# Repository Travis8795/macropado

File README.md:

# macropado
Macropado is a **8 key** macropad with a **rotary encoder** and an **OLED** screan and 8 SK6812 MINI-E Leds for **RGB** lights, it runs on **KMK** with python.

Here is a [video](https://youtu.be/G09okHm-6bo?si=OeQklzNeX-y66rIM) of it working

## CAD
Designed using **Fusion 360**.

The macropad is assembled by pressing heat-set inserts into the back of the top plate. Then, 16mm screws are inserted through the bottom of the base and the PCB, threading directly into the inserts to hold everything together.

| front | back |
| :---: | :---: |
|  |  |
|  |  |

## PCB
Designed using **KiCad**.

| Schematic | PCB |
| :---: | :---: |
|  |  |

## Firmware overview
Macropado runs on **KMK firmware** using CircuitPython for easy, "on-the-fly" customization.

* **Rotary Encoder:** Adjusts system volume with a press-to-mute function.
* **8 Programmable Keys:** Currently configured as custom macros for productivity.
* **OLED Screen:** Features a custom **Bongocat** animation! :3
* **RGB Lighting:** 8 addressable SK6812 MINI-E LEDs for dynamic status effects.

All logic is written in Python using KMK modules and extensions.

## BOM:
Here is **everything** you need to make this macropad

- 1x XIAO RP2040
- 8x Cherry MX Switches
- 8x DSA Keycaps
- 4x M3x5x4 Heatset inserts
- 4x M3x16mm screws
- 9x 1N4148 DO-35 Diodes.
- 8x SK6812 MINI-E LEDs
- 1x 0.91" 128x32 OLED Display
- 1x EC11 Rotary Encoder
- 1x Case (3 printed parts)

---
A huge shout-out to Hack Club and the Blueprint team!

I’ve dreamed of making this macropad for a long time, but I failed my previous attempts. Blueprint was the awesome opportunity I needed. The community support was amazing and helped me through the tough parts!

This was my first time ever using Fusion 360 for CAD, KiCad for PCB design, and my first time 'shipping' a complete GitHub repo. I learned so much during this YSWS journey. Thank you for everything—I owe you guys a lot! I'm so proud of my Macropado. <3

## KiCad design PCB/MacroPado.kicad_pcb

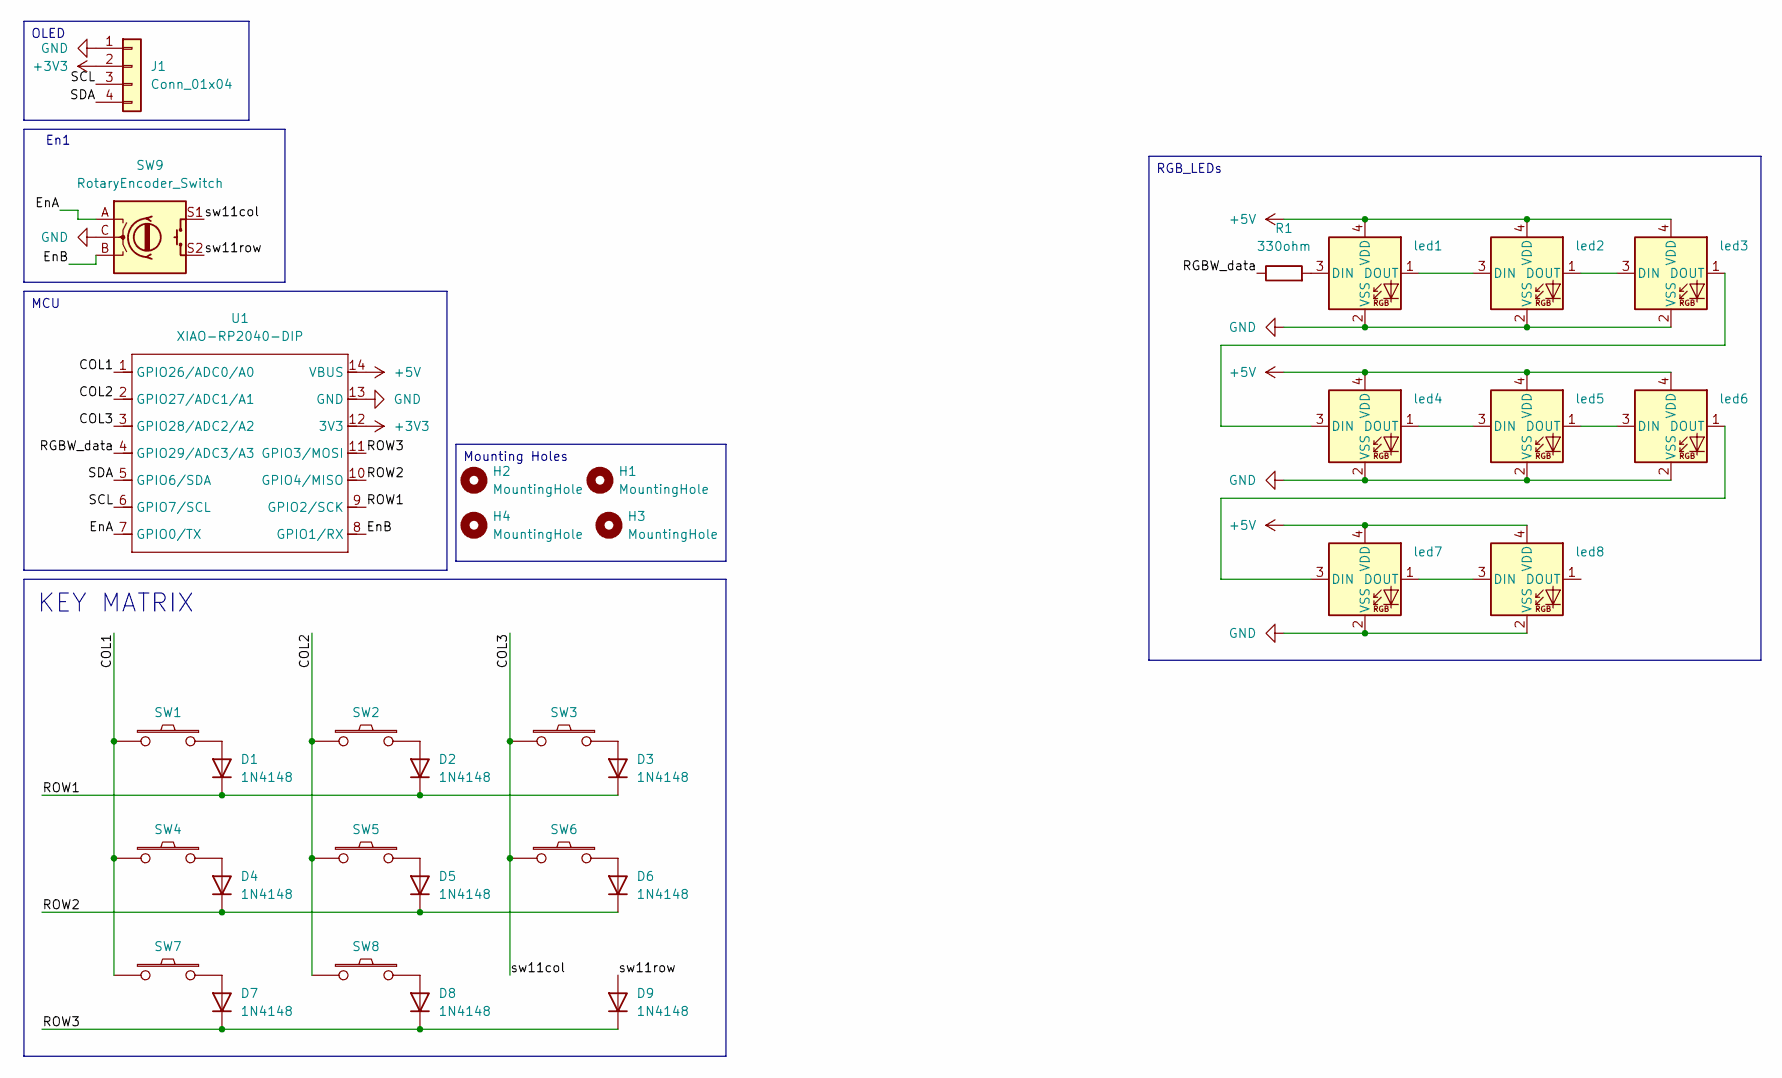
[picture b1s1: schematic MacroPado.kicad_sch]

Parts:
D1, D2, D3, D4, D5, D6, D7, D8, D9: 1N4148; D_DO-35_SOD27_P7.62mm_Horizontal
H1, H2, H3, H4: MountingHole; MountingHole_3.2mm_M3
J1: Conn_01x04; SSD1306-0.91-OLED-4pin-128x32
R1: 330ohm; R_Axial_DIN0204_L3.6mm_D1.6mm_P5.08mm_Horizontal
SW1, SW2, SW3, SW4, SW5, SW6, SW7, SW8: keyswitch; SW_Cherry_MX_1.00u_PCB; DigiKey Part Number MX2A-11NA
SW9: RotaryEncoder_Switch; RotaryEncoder_Alps_EC11E-Switch_Vertical_H20mm
U1: XIAO-RP2040-DIP
led1, led2, led3, led4, led5, led6, led7, led8: SK6812MINI; MX_SK6812MINI-E_REV

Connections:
+3V3: J1.2, U1.12 (3V3)
+5V: U1.14 (VBUS), led1.4 (VDD), led2.4 (VDD), led3.4 (VDD), led4.4 (VDD), led5.4 (VDD), led6.4 (VDD), led7.4 (VDD), led8.4 (VDD)
/COL1: SW1.2, SW4.2, SW7.2, U1.1 (GPIO26/ADC0/A0)
/COL2: SW2.2, SW5.2, SW8.2, U1.2 (GPIO27/ADC1/A1)
/COL3: SW3.2, SW6.2, SW9.S1, U1.3 (GPIO28/ADC2/A2)
/EnA: SW9.A, U1.7 (GPIO0/TX)
/EnB: SW9.B, U1.8 (GPIO1/RX)
/RGBW_data: R1.1, U1.4 (GPIO29/ADC3/A3)
/ROW1: D1.1 (K), D2.1 (K), D3.1 (K), U1.9 (GPIO2/SCK)
/ROW2: D4.1 (K), D5.1 (K), D6.1 (K), U1.10 (GPIO4/MISO)
/ROW3: D7.1 (K), D8.1 (K), D9.1 (K), U1.11 (GPIO3/MOSI)
/SCL: J1.3, U1.6 (GPIO7/SCL)
/SDA: J1.4, U1.5 (GPIO6/SDA)
/sw11row: D9.2 (A), SW9.S2
GND: J1.1, SW9.C, U1.13 (GND), led1.2 (VSS), led2.2 (VSS), led3.2 (VSS), led4.2 (VSS), led5.2 (VSS), led6.2 (VSS), led7.2 (VSS), led8.2 (VSS)
unnamed: D1.2 (A), SW1.1
unnamed: D2.2 (A), SW2.1
unnamed: D3.2 (A), SW3.1
unnamed: D4.2 (A), SW4.1
unnamed: D5.2 (A), SW5.1
unnamed: D6.2 (A), SW6.1
unnamed: D7.2 (A), SW7.1
unnamed: D8.2 (A), SW8.1
unnamed: R1.2, led1.3 (DIN)
unnamed: led1.1 (DOUT), led2.3 (DIN)
unnamed: led2.1 (DOUT), led3.3 (DIN)
unnamed: led3.1 (DOUT), led4.3 (DIN)
unnamed: led4.1 (DOUT), led5.3 (DIN)
unnamed: led5.1 (DOUT), led6.3 (DIN)
unnamed: led6.1 (DOUT), led7.3 (DIN)
unnamed: led7.1 (DOUT), led8.3 (DIN)

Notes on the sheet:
KEY MATRIX
En1
Mounting Holes
MCU
OLED
RGB_LEDs

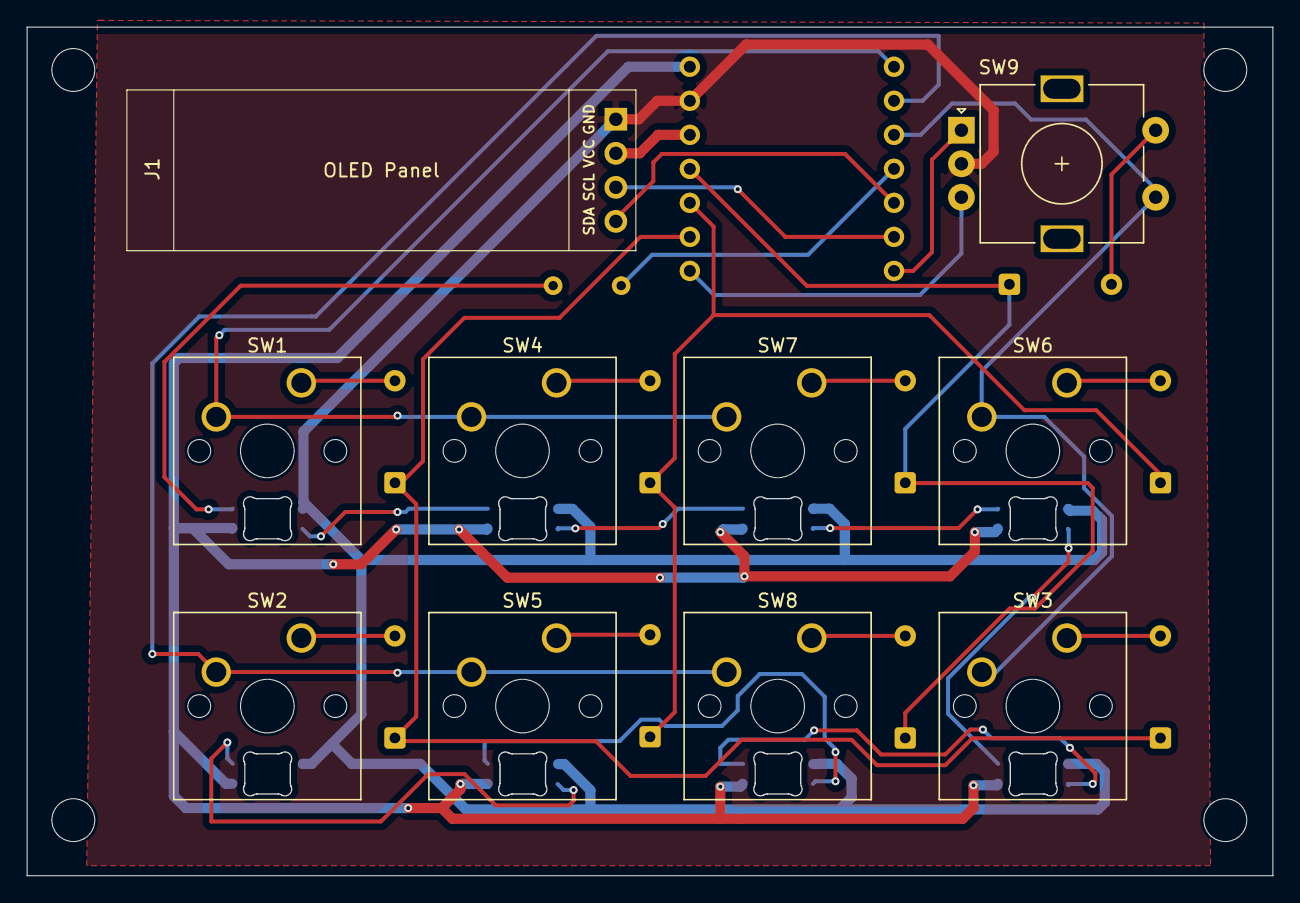
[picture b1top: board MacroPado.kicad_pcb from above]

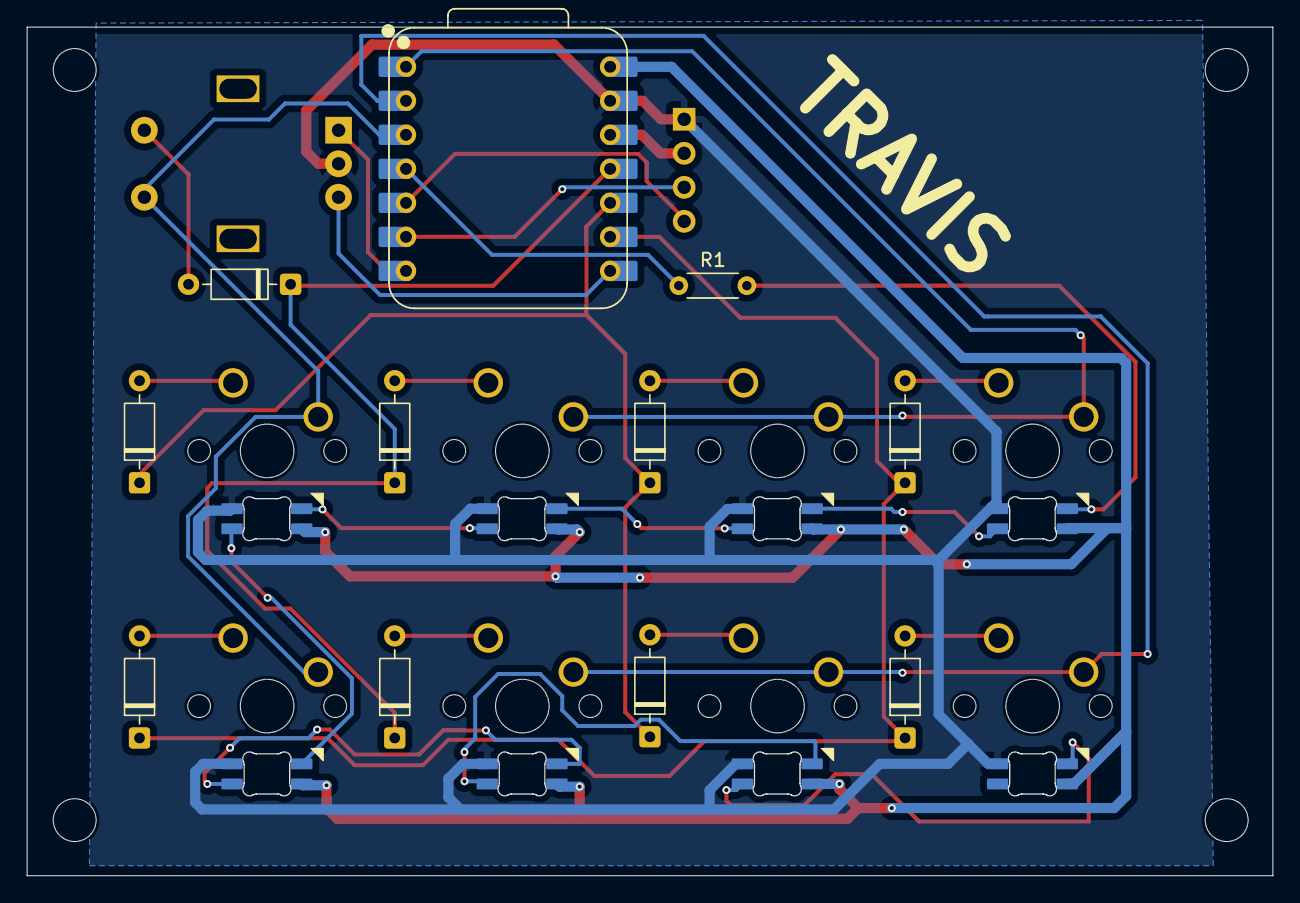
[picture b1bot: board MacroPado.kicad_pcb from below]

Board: 2 copper layers, 93.0 x 63.3 mm, 33 parts (11 on the bottom side), 31 nets.

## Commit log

2026-01-08 add CAD, Firmware, PCB
2026-01-08 Update README with schematic and PCB images
    Added schematic and PCB images to the README.
2026-01-08 Enhance README with detailed macropad information
    Expanded the README to provide detailed information about the macropad, including design, assembly instructions, PCB details, firmware overview, and a complete bill of materials.
2026-01-08 Update schematic image in README
2026-01-12 adding the bottom and plate files
2026-01-12 updating assembly file
2026-01-12 Update LED type from WS2812B to SK6812 MINI
2026-01-12 Fix LED model name in README
    Corrected the spelling of 'MINI' to 'MINI-E' for LEDs in multiple sections.
2026-03-09 Add flashing instructions for macropado
2026-03-09 Rename README.mk to README.md
2026-03-09 Enhance README with image and CAD information
    Added an image and CAD design details to the README.
2026-03-29 Update README with video link and image
    Added a video link and an image for the macropad.
